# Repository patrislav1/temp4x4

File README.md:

# temp4x4

A simple temperature measurement board supporting four 4-wire RTDs, using an ADS124S08.

Work in progress / under construction.

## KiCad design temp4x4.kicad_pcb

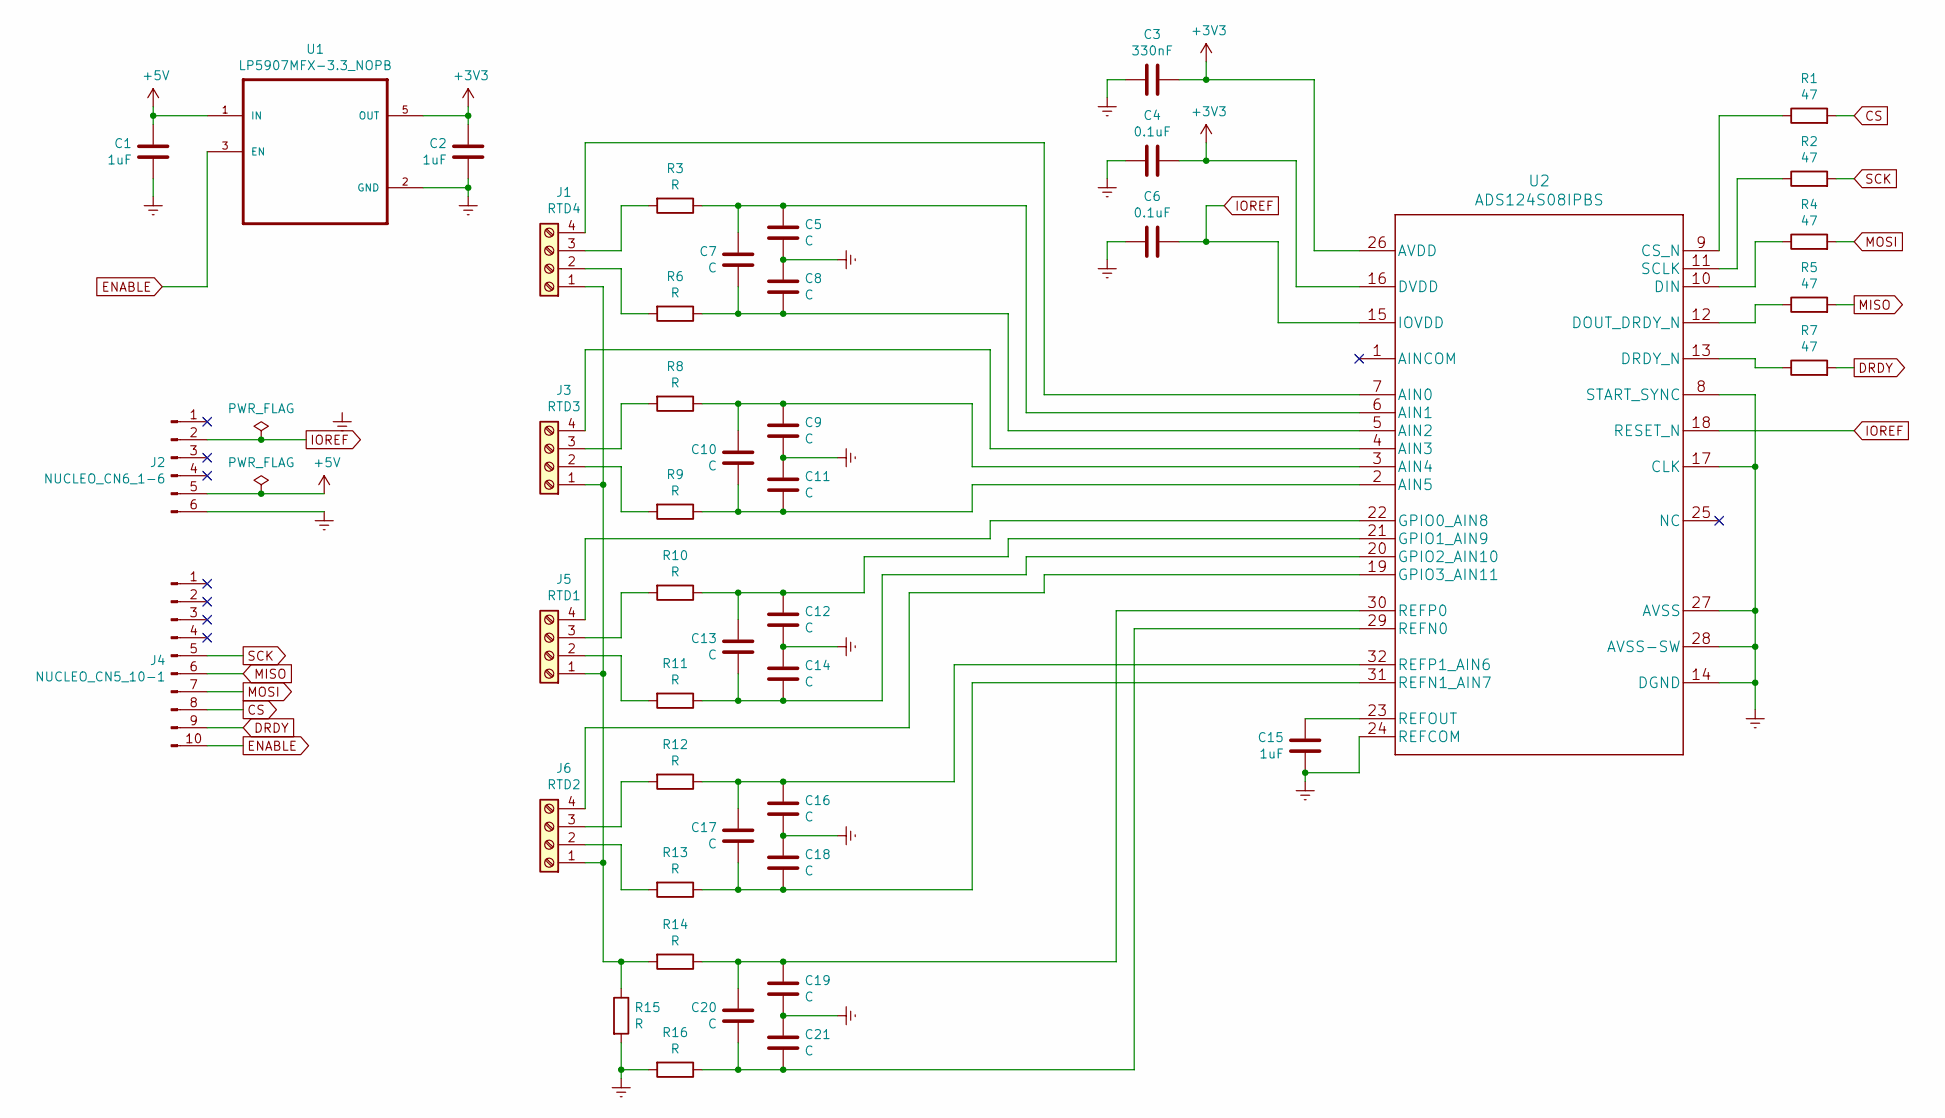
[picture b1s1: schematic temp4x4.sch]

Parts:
C1, C2, C15: 1uF; C_0805_2012Metric_Pad1.15x1.40mm_HandSolder
C3: 330nF; C_0805_2012Metric_Pad1.15x1.40mm_HandSolder
C4, C6: 0.1uF; C_0805_2012Metric_Pad1.15x1.40mm_HandSolder
C5, C7, C8, C9, C10, C11, C12, C13, C14, C16, C17, C18, C19, C20, C21: C; C_0805_2012Metric_Pad1.15x1.40mm_HandSolder
J1: RTD4; screw_term_4x
J2: NUCLEO_CN6_1-6; PinHeader_1x06_P2.54mm_Vertical
J3: RTD3; screw_term_4x
J4: NUCLEO_CN5_10-1; PinHeader_1x10_P2.54mm_Vertical
J5: RTD1; screw_term_4x
J6: RTD2; screw_term_4x
R1, R2, R4, R5, R7: 47; R_0805_2012Metric_Pad1.15x1.40mm_HandSolder
R3, R6, R8, R9, R10, R11, R12, R13, R14, R15, R16: R; R_0805_2012Metric_Pad1.15x1.40mm_HandSolder
U1: LP5907MFX-3.3_NOPB; SOT-23-5_HandSoldering
U2: ADS124S08IPBS; LQFP-32_5x5mm_P0.5mm

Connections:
+3V3: C2.1, C3.2, C4.2, U1.5 (OUT), U2.16 (DVDD), U2.26 (AVDD)
+5V: C1.1, J2.5, U1.1 (IN)
CS: J4.8, R1.2
DRDY: J4.9, R7.2
ENABLE: J4.10, U1.3 (EN)
Earth: C1.2, C2.2, C3.1, C4.1, C5.2, C6.1, C8.1, C9.2, C11.1, C12.2, C14.1, C15.2, C16.2, C18.1, C19.2, C21.1, J2.6, R15.2, R16.2, U1.2 (GND), U2.8 (START_SYNC), U2.14 (DGND), U2.17 (CLK), U2.24 (REFCOM), U2.27 (AVSS), U2.28 (AVSS-SW)
IOREF: C6.2, J2.2, U2.15 (IOVDD), U2.18 (RESET_N)
MISO: J4.6, R5.2
MOSI: J4.7, R4.2
unnamed: C5.1, C7.2, R3.1, U2.6 (AIN1)
unnamed: C7.1, C8.2, R6.1, U2.5 (AIN2)
unnamed: C10.1, C11.2, R9.1, U2.2 (AIN5)
unnamed: C9.1, C10.2, R8.1, U2.3 (AIN4)
unnamed: C12.1, C13.2, R10.1, U2.21 (GPIO1_AIN9)
unnamed: C13.1, C14.2, R11.1, U2.20 (GPIO2_AIN10)
unnamed: C15.1, U2.23 (REFOUT)
unnamed: C16.1, C17.2, R12.1, U2.32 (REFP1_AIN6)
unnamed: C17.1, C18.2, R13.1, U2.31 (REFN1_AIN7)
unnamed: C19.1, C20.2, R14.1, U2.30 (REFP0)
unnamed: C20.1, C21.2, R16.1, U2.29 (REFN0)
unnamed: J1.1, J3.1, J5.1, J6.1, R14.2, R15.1
unnamed: J1.2, R6.2
unnamed: J1.3, R3.2
unnamed: J1.4, U2.7 (AIN0)
unnamed: J3.2, R9.2
unnamed: J3.3, R8.2
unnamed: J3.4, U2.4 (AIN3)
unnamed: J5.2, R11.2
unnamed: J5.3, R10.2
unnamed: J5.4, U2.22 (GPIO0_AIN8)
unnamed: J6.2, R13.2
unnamed: J6.3, R12.2
unnamed: J6.4, U2.19 (GPIO3_AIN11)
unnamed: R1.1, U2.9 (CS_N)
unnamed: R2.1, U2.11 (SCLK)
unnamed: R4.1, U2.10 (DIN)
unnamed: R5.1, U2.12 (DOUT_DRDY_N)
unnamed: R7.1, U2.13 (DRDY_N)
SCK: J4.5, R2.2

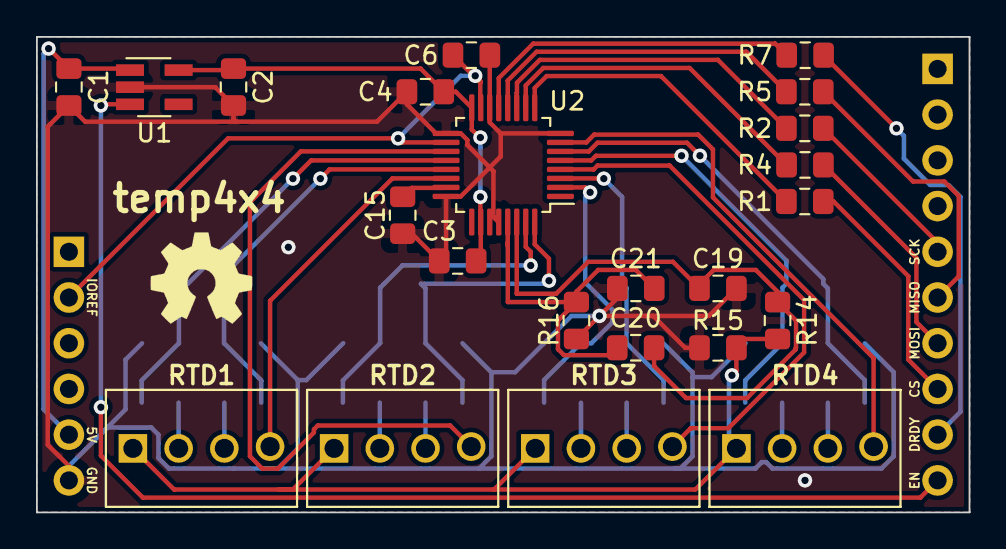
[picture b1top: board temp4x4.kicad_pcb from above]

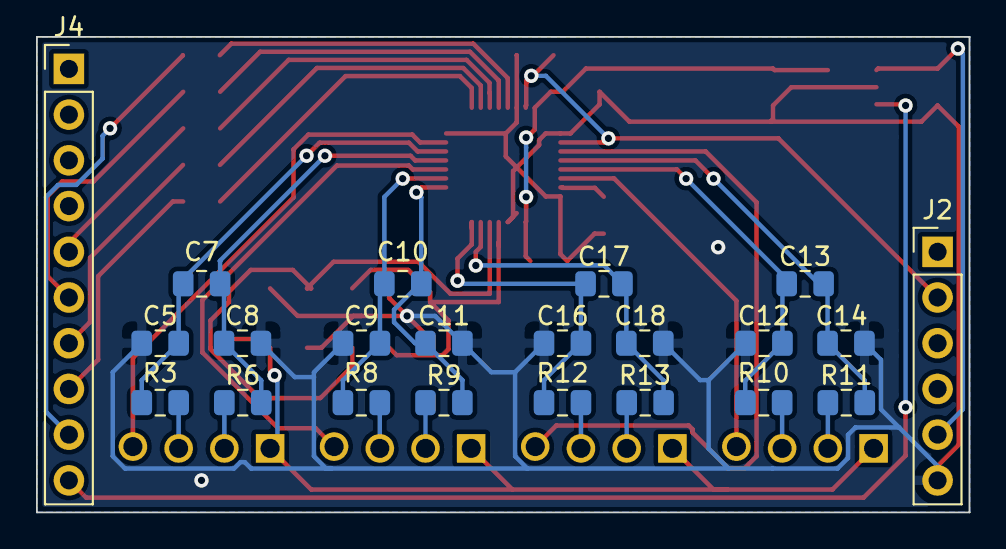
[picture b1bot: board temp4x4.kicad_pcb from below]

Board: 2 copper layers, 51.8 x 26.4 mm, 45 parts (22 on the bottom side), 39 nets.

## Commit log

2020-05-17 initial
2020-05-17 added KiCad footprints & symbols
2020-05-17 created symbol lib for project
2020-05-17 added footprints
2020-05-17 update schematic
2020-05-18 updated schematic
2020-05-18 added hierarchical sheet for RTDs
2020-05-18 Added second set of RTDs
2020-05-18 completed schematic
2020-05-18 finished schematic, assigned footprints, generated netlist
2020-05-18 added jumper to bypass 2nd RTD
2020-05-18 placed the components
2020-05-19 made board bigger to allow for better separation of analog / digital domains
2020-05-19 re-arranged parts for better digital / analog domain separation
2020-05-20 changed pin connections to simplify the layout
2020-05-20 added second GND connection through second pin header
2020-05-20 shrunk the vias a bit
2020-05-20 completed ground connections
2020-05-22 start re-doing the analog part
2020-05-22 re-done analog part of the circuit
2020-05-22 re-done layout
2020-05-22 added silkscreen labels
2020-05-22 added OSHW logo
2020-05-22 some PCB fine tuning
2020-05-22 don't check in backup files
2020-05-22 added README
